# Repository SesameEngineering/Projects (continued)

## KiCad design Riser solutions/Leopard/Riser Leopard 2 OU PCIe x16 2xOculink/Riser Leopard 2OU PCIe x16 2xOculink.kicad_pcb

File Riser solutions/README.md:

# Riser Solutions

Different riser solutions for OCP Leopard and OCP Tioga pass server are available. In those folders you can find different riser designs. For each you will have :
* Design files : all of the file required to do the design. Design has been made usiong Kicad
* Production files : files that you need for production, send all of them to your PCB manufacturer for production (it includes PCB, components and assembly)
* Test report : result of test that has been done to validate the designs

## Riser solutions for Leopard

### Riser 2 OU, 6x Oculink connector

On this riser we have 6 Oculink connector. Each connector is connected to 4 PCie lanes so we use the 24 PCie lanes available from Leopard server. This riser is used for storage solution since we can connect up to 6 U.2 form factor drives. A special cable, Oculink to U.2 has to be used to connect to each drives.

### Riser 2 OU, 1x connector PCIe x16 + 2x Oculink connector

On this riser we have 2 Oculink connector and one x16 PCIe connector. Each Oculink uses 4 PCIe lanes so in total we use the 24 PCIe lanes available from Leopard server. Oculink connectors can be connected to U.2 devices via a Oculink to U.2 cable. Any half length PCIe devices can be connected to the x16 PCIe connector (Ava Board, network card, HBA, small form factor GPUs, etc..).

### Riser 2 OU, 1x connector PCIe x8 + 4x Oculink connector

On this riser we have 4 Oculink connector and one x8 PCIe connector. Each Oculink uses 4 PCIe lanes so in total we use the 24 PCIe lanes available from Leopard server. Oculink connectors can be connected to U.2 devices via a Oculink to U.2 cable. Only x8 PCIe devices can be connected to the x8 PCIe connector.

### Riser 1 OU, 1x connector PCIe x16

This riser is for 1 OU form factor Leopard. There is only one x16 PCIe connector on it so we only use 16 PCIe lanes over the 24 PCIe lanes from Leopard server. Any half length PCIe devices can be connected to the x16 PCIe connector (Ava Board, network card, HBA, small form factor GPUs, etc..).

## Riser solutions for Tioga Pass

### Riser 2 OU, dual connector PCIe x16

This riser has been designed to provide riser to Tioga Pass servers. It has 2 x16 PCIe connectors so it uses the 32 PCIe lanes from Tioga Pass server. Any half length PCIe devices can be connected to the x16 PCIe connector (Ava Board, network card, HBA, small form factor GPUs, etc..). One full length GPU can be connector to the upper PCIe slot

### Riser 1 OU, 1x connector PCIe x16

This riser is for 1 OU form factor Tioga Pass. There is only one x16 PCIe connector on it so we only use 16 PCIe lanes over the 32 PCIe lanes from Tioga Pass server. Any half length PCIe devices can be connected to the x16 PCIe connector (Ava Board, network card, HBA, small form factor GPUs, etc..).

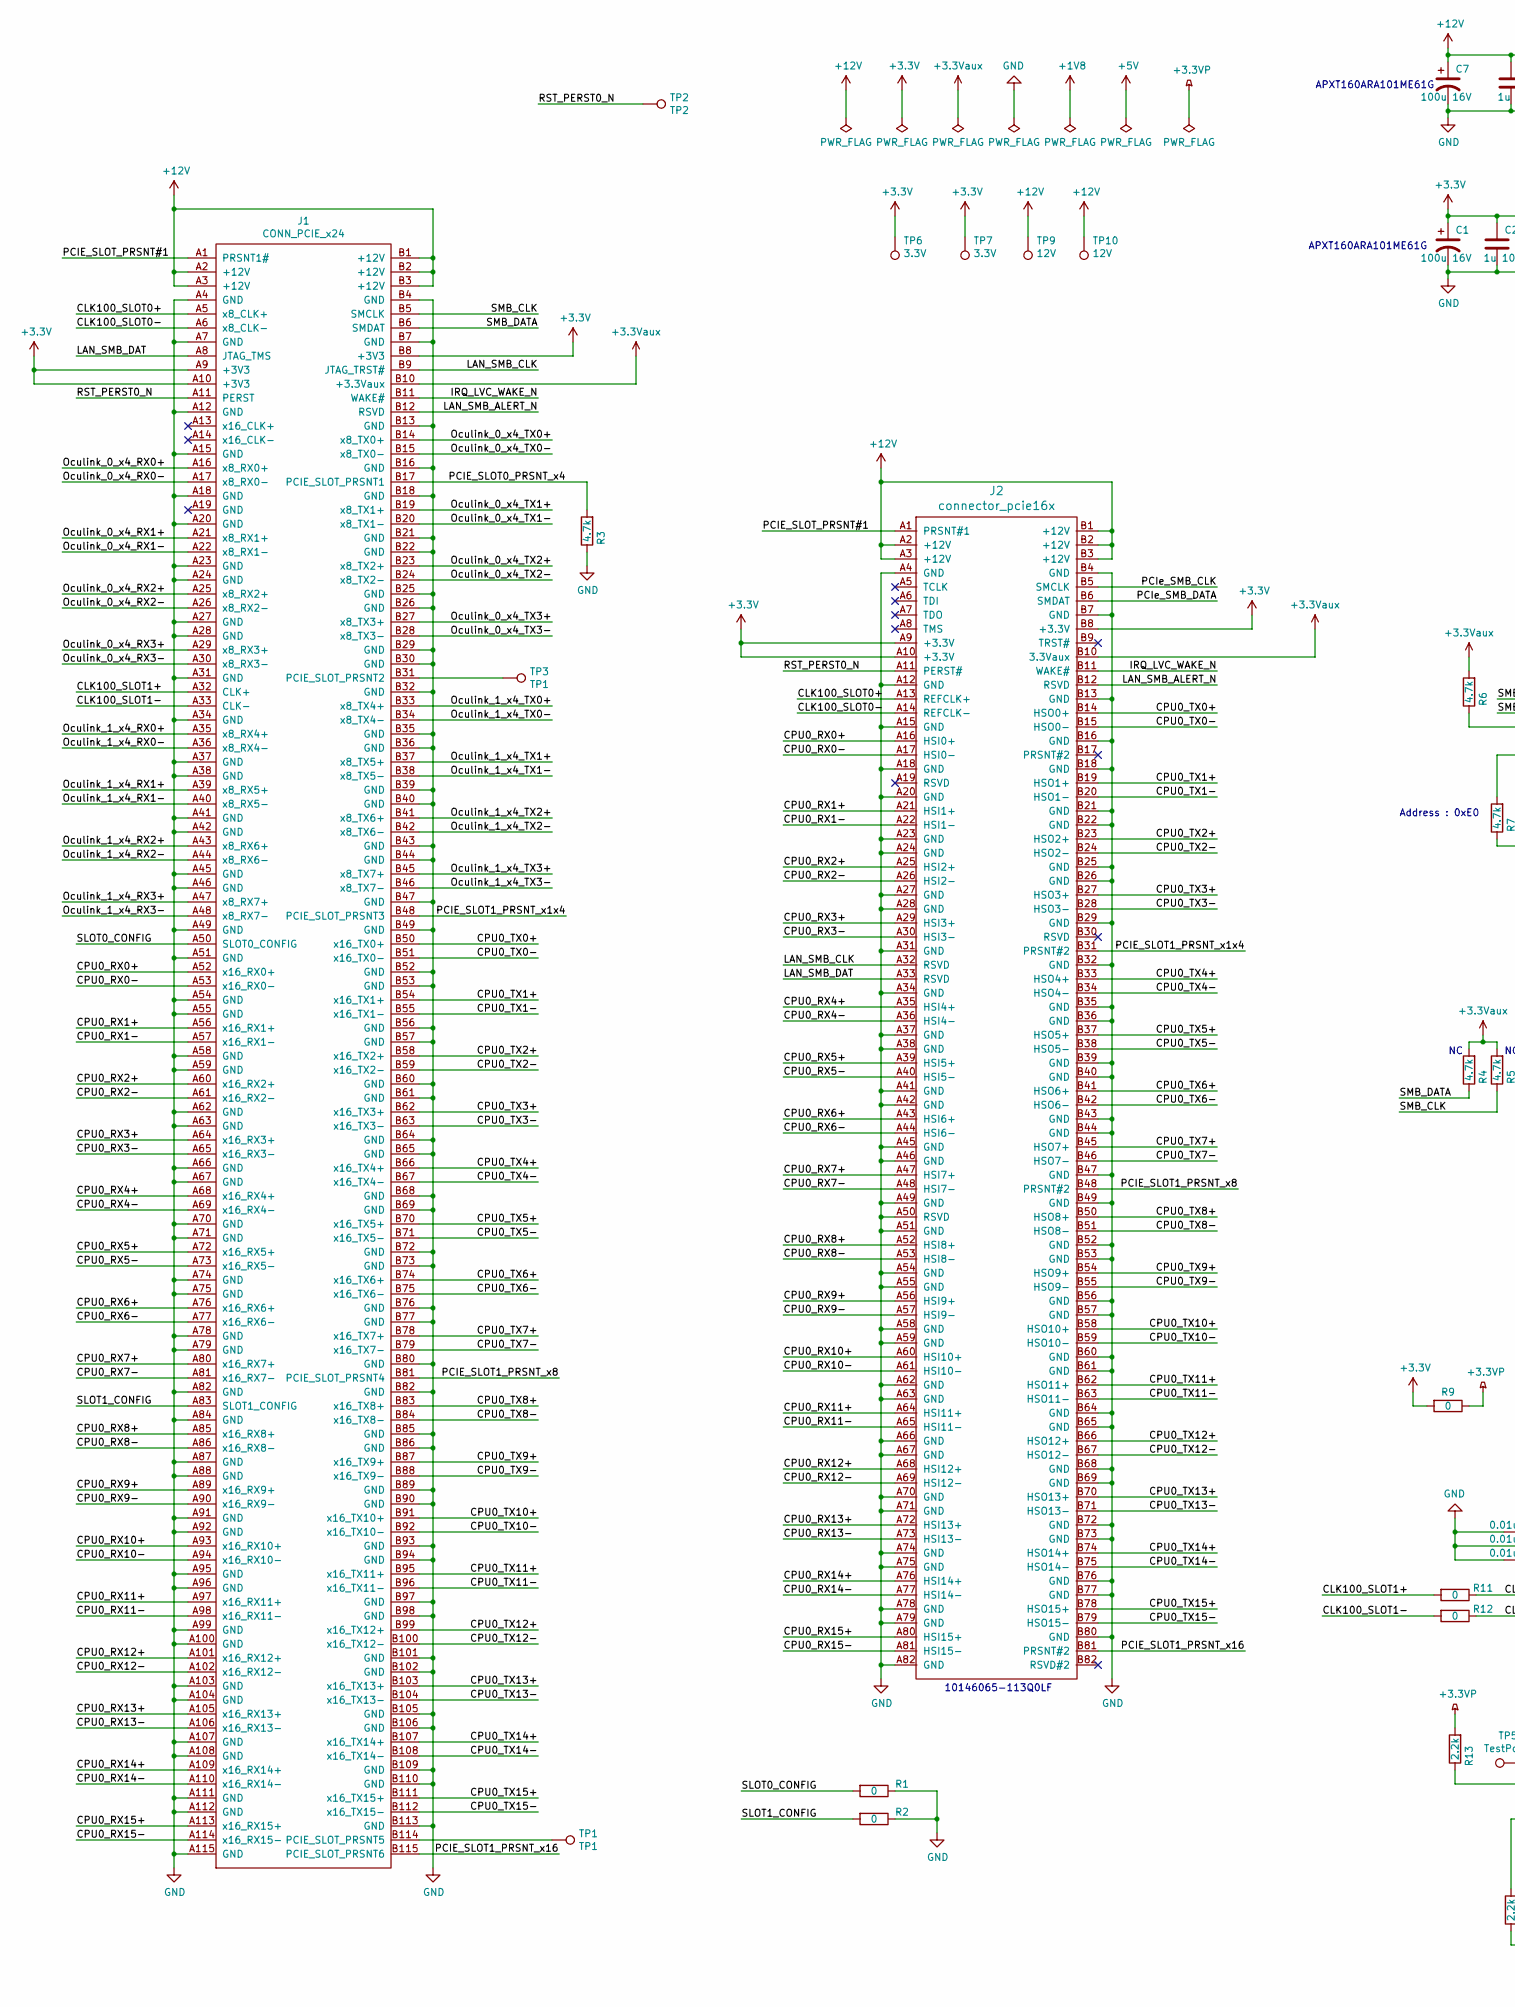
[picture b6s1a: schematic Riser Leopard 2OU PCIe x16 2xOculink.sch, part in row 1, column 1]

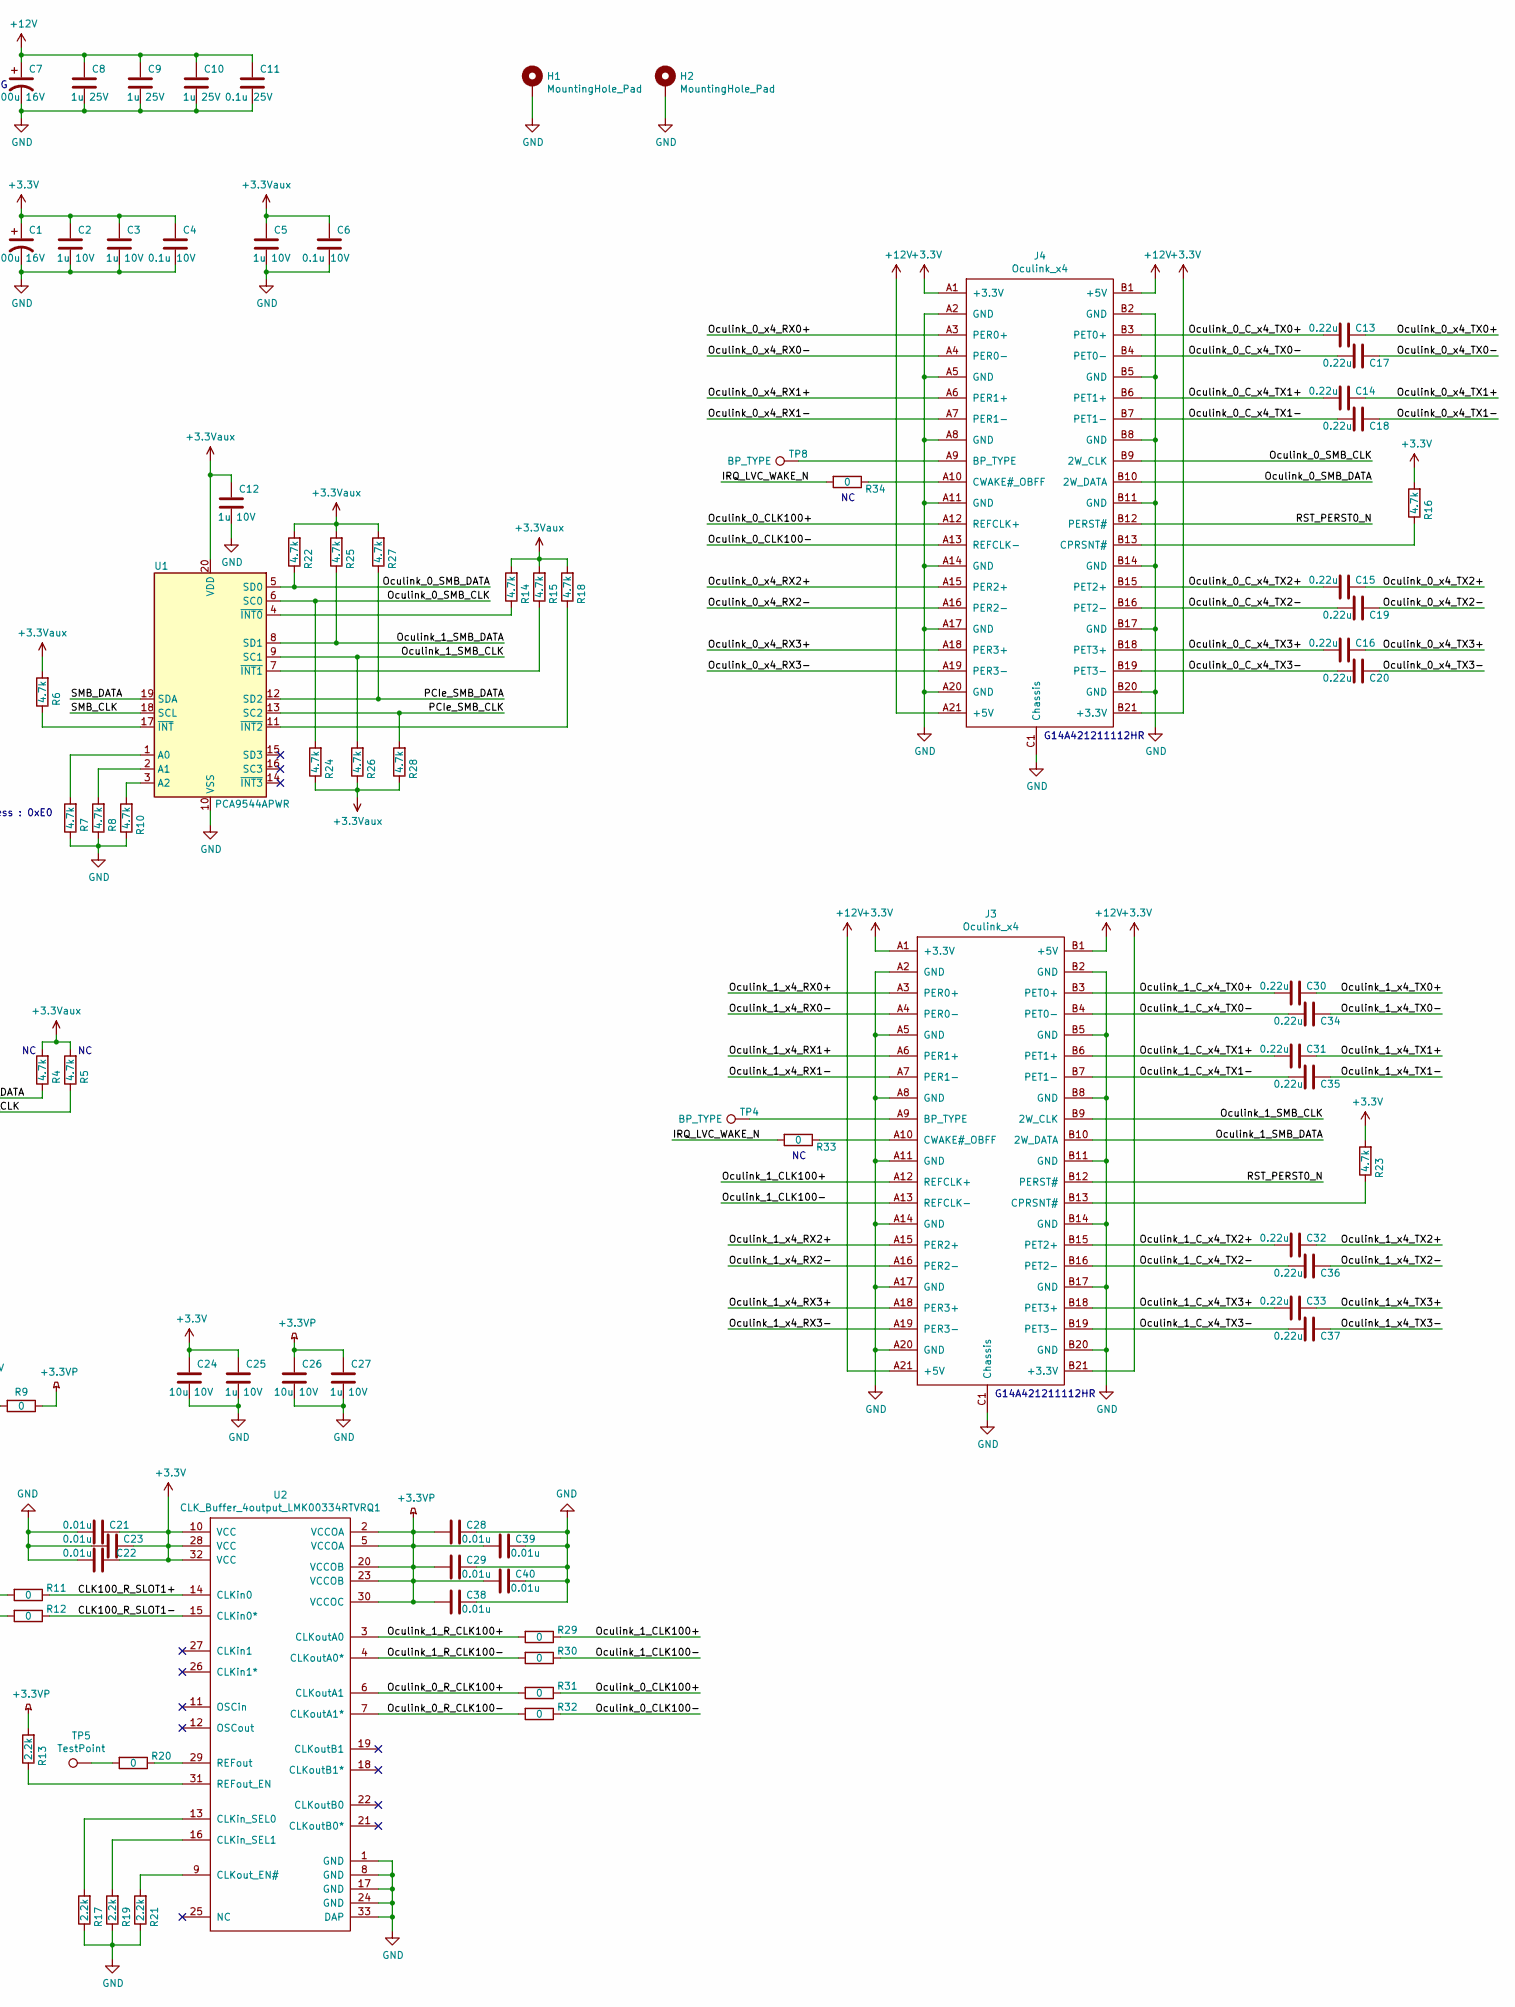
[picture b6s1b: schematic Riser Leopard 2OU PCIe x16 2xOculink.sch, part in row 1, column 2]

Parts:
C1, C7: 100u 16V; CapaElec_100u_16V_5.3x5.3mm
C2, C3, C5, C12, C25, C27: 1u 10V; C_0402
C4, C6: 0.1u 10V; C_0402
C8, C9, C10: 1u 25V; C_0603
C11: 0.1u 25V; C_0402
C13, C14, C15, C16, C17, C18, C19, C20, C30, C31, C32, C33, C34, C35, C36, C37: 0.22u; C_0201
C21, C22, C23, C28, C29, C38, C39, C40: 0.01u; C_0201
C24, C26: 10u 10V; C_0402
H1, H2: MountingHole_Pad; MountingHole_3.2mm_M3_Pad_Via
J1: CONN_PCIE_x24; pads_pcie_x24
J2: connector_pcie16x; pcie_16x
J3, J4: Oculink_x4; Oculink_x4_straight_G14A42221612AHR
R1, R2, R9, R11, R12, R20, R29, R30, R31, R32, R33, R34: 0; R_0402
R3, R4, R5, R6, R7, R8, R10, R14, R15, R16, R18, R22, R23, R24, R25, R26, R27, R28: 4.7k; R_0402
R13, R17, R19, R21: 2.2k; R_0402
TP1, TP3: TP1; TestPoint_Pad_D0.5mm
TP2: TP2; TestPoint_Pad_D0.5mm
TP4, TP8: BP_TYPE; TestPoint_Pad_D0.5mm
TP5: TestPoint; TestPoint_Pad_D0.5mm
TP6, TP7: 3.3V; TestPoint_Pad_D0.5mm
TP9, TP10: 12V; TestPoint_Pad_D0.5mm
U1: PCA9544APWR; TSSOP-20_4.4x6.5mm_Pitch0.65mm
U2: CLK_Buffer_4output_LMK00334RTVRQ1; WQFN-32-1EP_5x5mm_Pitch0.5mm

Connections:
+3.3VP: C26.1, C27.1, C28.2, C29.2, C38.2, C39.2, C40.2, R9.1, R13.2, U2.2 (VCCOA), U2.5 (VCCOA), U2.20 (VCCOB), U2.23 (VCCOB), U2.30 (VCCOC)
+3.3Vaux: C5.1, C6.1, C12.1, J1.B10 (+3.3Vaux), J2.B10 (3.3Vaux), R4.2, R5.2, R6.2, R14.2, R15.2, R18.2, R22.2, R24.1, R25.2, R26.1, R27.2, R28.1, U1.20 (VDD)
+3V3: C1.1, C2.1, C3.1, C4.1, C21.1, C22.1, C23.1, C24.1, C25.1, J1.A9 (+3V3), J1.A10 (+3V3), J1.B8 (+3V3), J2.A9 (+3.3V), J2.A10 (+3.3V), J2.B8 (+3.3V), J3.A1 (+3.3V), J3.B21 (+3.3V), J4.A1 (+3.3V), J4.B21 (+3.3V), R9.2, R16.2, R23.2, TP6.1, TP7.1, U2.10 (VCC), U2.28 (VCC), U2.32 (VCC); also elsewhere on the board
+12V: C7.1, C8.1, C9.1, C10.1, C11.1, J1.A2 (+12V), J1.A3 (+12V), J1.B1 (+12V), J1.B2 (+12V), J1.B3 (+12V), J2.A2 (+12V), J2.A3 (+12V), J2.B1 (+12V), J2.B2 (+12V), J2.B3 (+12V), J3.A21 (+5V), J3.B1 (+5V), J4.A21 (+5V), J4.B1 (+5V), TP9.1, TP10.1; also elsewhere on the board
/CLK100_R_SLOT1+: R11.1, U2.14 (CLKin0)
/CLK100_R_SLOT1-: R12.1, U2.15 (CLKin0*)
/CLK100_SLOT0+: J1.A5 (x8_CLK+), J2.A13 (REFCLK+)
/CLK100_SLOT0-: J1.A6 (x8_CLK-), J2.A14 (REFCLK-)
/CLK100_SLOT1+: J1.A32 (CLK+), R11.2
/CLK100_SLOT1-: J1.A33 (CLK-), R12.2
/CPU0_RX0+: J1.A52 (x16_RX0+), J2.A16 (HSI0+)
/CPU0_RX0-: J1.A53 (x16_RX0-), J2.A17 (HSI0-)
/CPU0_RX1+: J1.A56 (x16_RX1+), J2.A21 (HSI1+)
/CPU0_RX1-: J1.A57 (x16_RX1-), J2.A22 (HSI1-)
/CPU0_RX2+: J1.A60 (x16_RX2+), J2.A25 (HSI2+)
/CPU0_RX2-: J1.A61 (x16_RX2-), J2.A26 (HSI2-)
/CPU0_RX3+: J1.A64 (x16_RX3+), J2.A29 (HSI3+)
/CPU0_RX3-: J1.A65 (x16_RX3-), J2.A30 (HSI3-)
/CPU0_RX4+: J1.A68 (x16_RX4+), J2.A35 (HSI4+)
/CPU0_RX4-: J1.A69 (x16_RX4-), J2.A36 (HSI4-)
/CPU0_RX5+: J1.A72 (x16_RX5+), J2.A39 (HSI5+)
/CPU0_RX5-: J1.A73 (x16_RX5-), J2.A40 (HSI5-)
/CPU0_RX6+: J1.A76 (x16_RX6+), J2.A43 (HSI6+)
/CPU0_RX6-: J1.A77 (x16_RX6-), J2.A44 (HSI6-)
/CPU0_RX7+: J1.A80 (x16_RX7+), J2.A47 (HSI7+)
/CPU0_RX7-: J1.A81 (x16_RX7-), J2.A48 (HSI7-)
/CPU0_RX8+: J1.A85 (x16_RX8+), J2.A52 (HSI8+)
/CPU0_RX8-: J1.A86 (x16_RX8-), J2.A53 (HSI8-)
/CPU0_RX9+: J1.A89 (x16_RX9+), J2.A56 (HSI9+)
/CPU0_RX9-: J1.A90 (x16_RX9-), J2.A57 (HSI9-)
/CPU0_RX10+: J1.A93 (x16_RX10+), J2.A60 (HSI10+)
/CPU0_RX10-: J1.A94 (x16_RX10-), J2.A61 (HSI10-)
/CPU0_RX11+: J1.A97 (x16_RX11+), J2.A64 (HSI11+)
/CPU0_RX11-: J1.A98 (x16_RX11-), J2.A65 (HSI11-)
/CPU0_RX12+: J1.A101 (x16_RX12+), J2.A68 (HSI12+)
/CPU0_RX12-: J1.A102 (x16_RX12-), J2.A69 (HSI12-)
/CPU0_RX13+: J1.A105 (x16_RX13+), J2.A72 (HSI13+)
/CPU0_RX13-: J1.A106 (x16_RX13-), J2.A73 (HSI13-)
/CPU0_RX14+: J1.A109 (x16_RX14+), J2.A76 (HSI14+)
/CPU0_RX14-: J1.A110 (x16_RX14-), J2.A77 (HSI14-)
/CPU0_RX15+: J1.A113 (x16_RX15+), J2.A80 (HSI15+)
/CPU0_RX15-: J1.A114 (x16_RX15-), J2.A81 (HSI15-)
/CPU0_TX0+: J1.B50 (x16_TX0+), J2.B14 (HSO0+)
/CPU0_TX0-: J1.B51 (x16_TX0-), J2.B15 (HSO0-)
/CPU0_TX1+: J1.B54 (x16_TX1+), J2.B19 (HSO1+)
/CPU0_TX1-: J1.B55 (x16_TX1-), J2.B20 (HSO1-)
/CPU0_TX2+: J1.B58 (x16_TX2+), J2.B23 (HSO2+)
/CPU0_TX2-: J1.B59 (x16_TX2-), J2.B24 (HSO2-)
/CPU0_TX3+: J1.B62 (x16_TX3+), J2.B27 (HSO3+)
/CPU0_TX3-: J1.B63 (x16_TX3-), J2.B28 (HSO3-)
/CPU0_TX4+: J1.B66 (x16_TX4+), J2.B33 (HSO4+)
/CPU0_TX4-: J1.B67 (x16_TX4-), J2.B34 (HSO4-)
/CPU0_TX5+: J1.B70 (x16_TX5+), J2.B37 (HSO5+)
/CPU0_TX5-: J1.B71 (x16_TX5-), J2.B38 (HSO5-)
/CPU0_TX6+: J1.B74 (x16_TX6+), J2.B41 (HSO6+)
/CPU0_TX6-: J1.B75 (x16_TX6-), J2.B42 (HSO6-)
/CPU0_TX7+: J1.B78 (x16_TX7+), J2.B45 (HSO7+)
/CPU0_TX7-: J1.B79 (x16_TX7-), J2.B46 (HSO7-)
/CPU0_TX8+: J1.B83 (x16_TX8+), J2.B50 (HSO8+)
/CPU0_TX8-: J1.B84 (x16_TX8-), J2.B51 (HSO8-)
/CPU0_TX9+: J1.B87 (x16_TX9+), J2.B54 (HSO9+)
/CPU0_TX9-: J1.B88 (x16_TX9-), J2.B55 (HSO9-)
/CPU0_TX10+: J1.B91 (x16_TX10+), J2.B58 (HSO10+)
/CPU0_TX10-: J1.B92 (x16_TX10-), J2.B59 (HSO10-)
/CPU0_TX11+: J1.B95 (x16_TX11+), J2.B62 (HSO11+)
/CPU0_TX11-: J1.B96 (x16_TX11-), J2.B63 (HSO11-)
/CPU0_TX12+: J1.B99 (x16_TX12+), J2.B66 (HSO12+)
/CPU0_TX12-: J1.B100 (x16_TX12-), J2.B67 (HSO12-)
/CPU0_TX13+: J1.B103 (x16_TX13+), J2.B70 (HSO13+)
/CPU0_TX13-: J1.B104 (x16_TX13-), J2.B71 (HSO13-)
/CPU0_TX14+: J1.B107 (x16_TX14+), J2.B74 (HSO14+)
/CPU0_TX14-: J1.B108 (x16_TX14-), J2.B75 (HSO14-)
/CPU0_TX15+: J1.B111 (x16_TX15+), J2.B78 (HSO15+)
/CPU0_TX15-: J1.B112 (x16_TX15-), J2.B79 (HSO15-)
/IRQ_LVC_WAKE_N: J1.B11 (WAKE#), J2.B11 (WAKE#), R33.2, R34.2
/LAN_SMB_ALERT_N: J1.B12 (RSVD), J2.B12 (RSVD)
/LAN_SMB_CLK: J1.B9 (JTAG_TRST#), J2.A32 (RSVD)
/LAN_SMB_DAT: J1.A8 (JTAG_TMS), J2.A33 (RSVD)
/Oculink_0_CLK100+: J4.A12 (REFCLK+), R31.1
/Oculink_0_CLK100-: J4.A13 (REFCLK-), R32.1
/Oculink_0_C_x4_TX0+: C13.2, J4.B3 (PET0+)
/Oculink_0_C_x4_TX0-: C17.2, J4.B4 (PET0-)
/Oculink_0_C_x4_TX1+: C14.2, J4.B6 (PET1+)
/Oculink_0_C_x4_TX1-: C18.2, J4.B7 (PET1-)
/Oculink_0_C_x4_TX2+: C15.2, J4.B15 (PET2+)
/Oculink_0_C_x4_TX2-: C19.2, J4.B16 (PET2-)
/Oculink_0_C_x4_TX3+: C16.2, J4.B18 (PET3+)
/Oculink_0_C_x4_TX3-: C20.2, J4.B19 (PET3-)
/Oculink_0_R_CLK100+: R31.2, U2.6 (CLKoutA1)
/Oculink_0_R_CLK100-: R32.2, U2.7 (CLKoutA1*)
/Oculink_0_SMB_CLK: J4.B9 (2W_CLK), R24.2, U1.6 (SC0)
/Oculink_0_SMB_DATA: J4.B10 (2W_DATA), R22.1, U1.5 (SD0)
/Oculink_0_x4_RX0+: J1.A16 (x8_RX0+), J4.A3 (PER0+)
/Oculink_0_x4_RX0-: J1.A17 (x8_RX0-), J4.A4 (PER0-)
/Oculink_0_x4_RX1+: J1.A21 (x8_RX1+), J4.A6 (PER1+)
/Oculink_0_x4_RX1-: J1.A22 (x8_RX1-), J4.A7 (PER1-)
/Oculink_0_x4_RX2+: J1.A25 (x8_RX2+), J4.A15 (PER2+)
/Oculink_0_x4_RX2-: J1.A26 (x8_RX2-), J4.A16 (PER2-)
/Oculink_0_x4_RX3+: J1.A29 (x8_RX3+), J4.A18 (PER3+)
/Oculink_0_x4_RX3-: J1.A30 (x8_RX3-), J4.A19 (PER3-)
/Oculink_0_x4_TX0+: C13.1, J1.B14 (x8_TX0+)
/Oculink_0_x4_TX0-: C17.1, J1.B15 (x8_TX0-)
/Oculink_0_x4_TX1+: C14.1, J1.B19 (x8_TX1+)
/Oculink_0_x4_TX1-: C18.1, J1.B20 (x8_TX1-)
/Oculink_0_x4_TX2+: C15.1, J1.B23 (x8_TX2+)
/Oculink_0_x4_TX2-: C19.1, J1.B24 (x8_TX2-)
/Oculink_0_x4_TX3+: C16.1, J1.B27 (x8_TX3+)
/Oculink_0_x4_TX3-: C20.1, J1.B28 (x8_TX3-)
/Oculink_1_CLK100+: J3.A12 (REFCLK+), R29.1
/Oculink_1_CLK100-: J3.A13 (REFCLK-), R30.1
/Oculink_1_C_x4_TX0+: C30.2, J3.B3 (PET0+)
/Oculink_1_C_x4_TX0-: C34.2, J3.B4 (PET0-)
/Oculink_1_C_x4_TX1+: C31.2, J3.B6 (PET1+)
/Oculink_1_C_x4_TX1-: C35.2, J3.B7 (PET1-)
/Oculink_1_C_x4_TX2+: C32.2, J3.B15 (PET2+)
/Oculink_1_C_x4_TX2-: C36.2, J3.B16 (PET2-)
/Oculink_1_C_x4_TX3+: C33.2, J3.B18 (PET3+)
/Oculink_1_C_x4_TX3-: C37.2, J3.B19 (PET3-)
/Oculink_1_R_CLK100+: R29.2, U2.3 (CLKoutA0)
/Oculink_1_R_CLK100-: R30.2, U2.4 (CLKoutA0*)
/Oculink_1_SMB_CLK: J3.B9 (2W_CLK), R26.2, U1.9 (SC1)
/Oculink_1_SMB_DATA: J3.B10 (2W_DATA), R25.1, U1.8 (SD1)
/Oculink_1_x4_RX0+: J1.A35 (x8_RX4+), J3.A3 (PER0+)
/Oculink_1_x4_RX0-: J1.A36 (x8_RX4-), J3.A4 (PER0-)
/Oculink_1_x4_RX1+: J1.A39 (x8_RX5+), J3.A6 (PER1+)
/Oculink_1_x4_RX1-: J1.A40 (x8_RX5-), J3.A7 (PER1-)
/Oculink_1_x4_RX2+: J1.A43 (x8_RX6+), J3.A15 (PER2+)
/Oculink_1_x4_RX2-: J1.A44 (x8_RX6-), J3.A16 (PER2-)
/Oculink_1_x4_RX3+: J1.A47 (x8_RX7+), J3.A18 (PER3+)
/Oculink_1_x4_RX3-: J1.A48 (x8_RX7-), J3.A19 (PER3-)
/Oculink_1_x4_TX0+: C30.1, J1.B33 (x8_TX4+)
/Oculink_1_x4_TX0-: C34.1, J1.B34 (x8_TX4-)
/Oculink_1_x4_TX1+: C31.1, J1.B37 (x8_TX5+)
/Oculink_1_x4_TX1-: C35.1, J1.B38 (x8_TX5-)
/Oculink_1_x4_TX2+: C32.1, J1.B41 (x8_TX6+)
/Oculink_1_x4_TX2-: C36.1, J1.B42 (x8_TX6-)
/Oculink_1_x4_TX3+: C33.1, J1.B45 (x8_TX7+)
/Oculink_1_x4_TX3-: C37.1, J1.B46 (x8_TX7-)
/PCIE_SLOT0_PRSNT_x4: J1.B17 (PCIE_SLOT_PRSNT1), R3.2
/PCIE_SLOT1_PRSNT_x1x4: J1.B48 (PCIE_SLOT_PRSNT3), J2.B31 (PRSNT#2)
/PCIE_SLOT1_PRSNT_x8: J1.B81 (PCIE_SLOT_PRSNT4), J2.B48 (PRSNT#2)
/PCIE_SLOT1_PRSNT_x16: J1.B115 (PCIE_SLOT_PRSNT6), J2.B81 (PRSNT#2)
/PCIE_SLOT_PRSNT#1: J1.A1 (PRSNT1#), J2.A1 (PRSNT#1)
/PCIe_SMB_CLK: J2.B5 (SMCLK), R28.2, U1.13 (SC2)
/PCIe_SMB_DATA: J2.B6 (SMDAT), R27.1, U1.12 (SD2)
/RST_PERST0_N: J1.A11 (PERST), J2.A11 (PERST#), J3.B12 (PERST#), J4.B12 (PERST#), TP2.1
/SLOT0_CONFIG: J1.A50 (SLOT0_CONFIG), R1.2
/SLOT1_CONFIG: J1.A83 (SLOT1_CONFIG), R2.2
/SMB_CLK: J1.B5 (SMCLK), R5.1, U1.18 (SCL)
/SMB_DATA: J1.B6 (SMDAT), R4.1, U1.19 (SDA)
GND: C1.2, C2.2, C3.2, C4.2, C5.2, C6.2, C7.2, C8.2, C9.2, C10.2, C11.2, C12.2, C21.2, C22.2, C23.2, C24.2, C25.2, C26.2, C27.2, C28.1, C29.1, C38.1, C39.1, C40.1, H1.1, H2.1, J1.A4 (GND), J1.A7 (GND), J1.A12 (GND), J1.A15 (GND), J1.A18 (GND), J1.A20 (GND), J1.A23 (GND), J1.A24 (GND), J1.A27 (GND), J1.A28 (GND), J1.A31 (GND), J1.A34 (GND), J1.A37 (GND), J1.A38 (GND), J1.A41 (GND), J1.A42 (GND), J1.A45 (GND), J1.A46 (GND), J1.A49 (GND), J1.A51 (GND), J1.A54 (GND), J1.A55 (GND), J1.A58 (GND), J1.A59 (GND), J1.A62 (GND), J1.A63 (GND), J1.A66 (GND), J1.A67 (GND), J1.A70 (GND), J1.A71 (GND), J1.A74 (GND), J1.A75 (GND), J1.A78 (GND), J1.A79 (GND), J1.A82 (GND), J1.A84 (GND), J1.A87 (GND), J1.A88 (GND), J1.A91 (GND), J1.A92 (GND), J1.A95 (GND), J1.A96 (GND), J1.A99 (GND), J1.A100 (GND), J1.A103 (GND), J1.A104 (GND), J1.A107 (GND), J1.A108 (GND), J1.A111 (GND), J1.A112 (GND), J1.A115 (GND), J1.B4 (GND), J1.B7 (GND), J1.B13 (GND), J1.B16 (GND), J1.B18 (GND), J1.B21 (GND), J1.B22 (GND), J1.B25 (GND), J1.B26 (GND), J1.B29 (GND), J1.B30 (GND), J1.B32 (GND), J1.B35 (GND), J1.B36 (GND), J1.B39 (GND), J1.B40 (GND), J1.B43 (GND), J1.B44 (GND), J1.B47 (GND), J1.B49 (GND), J1.B52 (GND), J1.B53 (GND), J1.B56 (GND), J1.B57 (GND), J1.B60 (GND), J1.B61 (GND), J1.B64 (GND), J1.B65 (GND), J1.B68 (GND), J1.B69 (GND), J1.B72 (GND), J1.B73 (GND), J1.B76 (GND), J1.B77 (GND), J1.B80 (GND), J1.B82 (GND), J1.B85 (GND), J1.B86 (GND), J1.B89 (GND), J1.B90 (GND), J1.B93 (GND), J1.B94 (GND), J1.B97 (GND), J1.B98 (GND), J1.B101 (GND), J1.B102 (GND), J1.B105 (GND), J1.B106 (GND), J1.B109 (GND), J1.B110 (GND), J1.B113 (GND), J2.A4 (GND), J2.A12 (GND), J2.A15 (GND), J2.A18 (GND), J2.A20 (GND), J2.A23 (GND), J2.A24 (GND), J2.A27 (GND), J2.A28 (GND), J2.A31 (GND), J2.A34 (GND), J2.A37 (GND), J2.A38 (GND), J2.A41 (GND), J2.A42 (GND), J2.A45 (GND), J2.A46 (GND), J2.A49 (GND), J2.A50 (RSVD), J2.A51 (GND), J2.A54 (GND), J2.A55 (GND), J2.A58 (GND), J2.A59 (GND), J2.A62 (GND), J2.A63 (GND), J2.A66 (GND), J2.A67 (GND), J2.A70 (GND), J2.A71 (GND), J2.A74 (GND), J2.A75 (GND), J2.A78 (GND), J2.A79 (GND), J2.A82 (GND), J2.B4 (GND), J2.B7 (GND), J2.B13 (GND), J2.B16 (GND), J2.B18 (GND), J2.B21 (GND), J2.B22 (GND), J2.B25 (GND), J2.B26 (GND), J2.B29 (GND), J2.B32 (GND), J2.B35 (GND), J2.B36 (GND), J2.B39 (GND), J2.B40 (GND), J2.B43 (GND), J2.B44 (GND), J2.B47 (GND), J2.B49 (GND), J2.B52 (GND), J2.B53 (GND), J2.B56 (GND), J2.B57 (GND), J2.B60 (GND), J2.B61 (GND), J2.B64 (GND), J2.B65 (GND), J2.B68 (GND), J2.B69 (GND), J2.B72 (GND), J2.B73 (GND), J2.B76 (GND), J2.B77 (GND), J2.B80 (GND), J3.A2 (GND), J3.A5 (GND), J3.A8 (GND), J3.A11 (GND), J3.A14 (GND), J3.A17 (GND), J3.A20 (GND), J3.B2 (GND), J3.B5 (GND), J3.B8 (GND), J3.B11 (GND), J3.B14 (GND), J3.B17 (GND), J3.B20 (GND), J3.C1 (Chassis), J4.A2 (GND), J4.A5 (GND), J4.A8 (GND), J4.A11 (GND), J4.A14 (GND), J4.A17 (GND), J4.A20 (GND), J4.B2 (GND), J4.B5 (GND), J4.B8 (GND), J4.B11 (GND), J4.B14 (GND), J4.B17 (GND), J4.B20 (GND), J4.C1 (Chassis), R1.1, R2.1, R3.1, R7.1, R8.1, R10.1, R17.1, R19.1, R21.1, U1.10 (VSS), U2.1 (GND), U2.8 (GND), U2.17 (GND), U2.24 (GND), U2.33 (DAP)
unnamed: J1.B31 (PCIE_SLOT_PRSNT2), TP3.1
unnamed: J1.B114 (PCIE_SLOT_PRSNT5), TP1.1
unnamed: J3.A9 (BP_TYPE), TP4.1
unnamed: J3.A10 (CWAKE#_OBFF), R33.1
unnamed: J3.B13 (CPRSNT#), R23.1
unnamed: J4.A9 (BP_TYPE), TP8.1
unnamed: J4.A10 (CWAKE#_OBFF), R34.1
unnamed: J4.B13 (CPRSNT#), R16.1
unnamed: R6.1, U1.17 (~INT)
unnamed: R7.2, U1.1 (A0)
unnamed: R8.2, U1.2 (A1)
unnamed: R10.2, U1.3 (A2)
unnamed: R13.1, U2.31 (REFout_EN)
unnamed: R14.1, U1.4 (~INT0)
unnamed: R15.1, U1.7 (~INT1)
unnamed: R17.2, U2.13 (CLKin_SEL0)
unnamed: R18.1, U1.11 (~INT2)
unnamed: R19.2, U2.16 (CLKin_SEL1)
unnamed: R20.1, U2.29 (REFout)
unnamed: R20.2, TP5.1
unnamed: R21.2, U2.9 (CLKout_EN#)

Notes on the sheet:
APXT160ARA101ME61G
10146065-113Q0LF
G14A421211112HR
Address : 0xE0

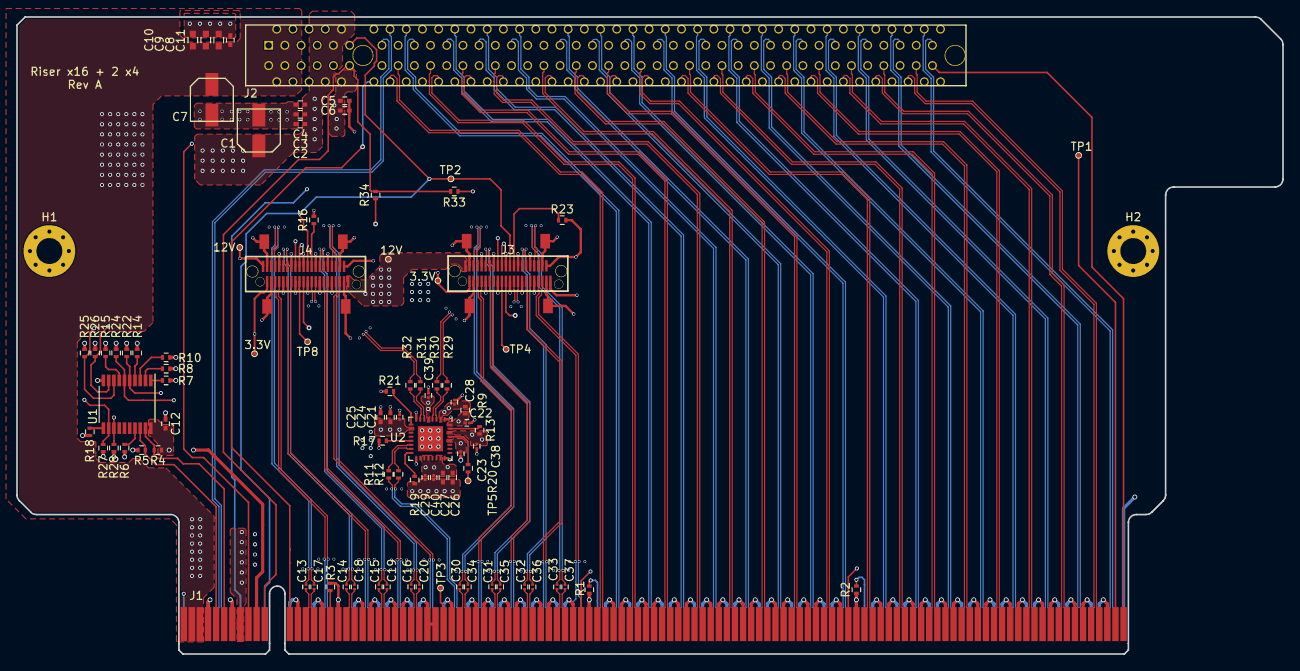
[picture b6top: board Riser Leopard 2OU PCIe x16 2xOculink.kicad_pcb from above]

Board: 6 copper layers, 156.4 x 78.7 mm, 92 parts (0 on the bottom side), 172 nets.

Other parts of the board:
3.3V, 3.3V#2: 3.3V; TestPoint_Pad_D0.5mm
12V, 12V#2: 12V; TestPoint_Pad_D0.5mm

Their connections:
+3V3: 3.3V.1, 3.3V#2.1; also elsewhere on the board
+12V: 12V.1, 12V#2.1; also elsewhere on the board

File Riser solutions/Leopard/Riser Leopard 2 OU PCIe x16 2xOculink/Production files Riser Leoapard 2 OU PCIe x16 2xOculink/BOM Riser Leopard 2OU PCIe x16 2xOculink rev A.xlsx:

Id | Reference | Footprint | Quantity | Designation | Manufacturer | Manufacturer part number
1 | C1,C7 | CapaElec_100u_16V_5.3x5.3mm | 2 | 100u 16V | Panasonic | EEE-FN1C101UR
2 | C2,C3,C5,C12,C25,C27 | C_0402 | 6 | 1u 10V | Taiyo Yuden | LMK105BJ105MVHF
3 | C4,C6 | C_0402 | 2 | 0.1u 10V | Taiyo Yuden | LMF105B7104MVHF
4 | C8,C9,C10 | C_0603 | 3 | 1u 25V | Taiyo Yuden | TMK107B7105KA-T
5 | C11 | C_0402 | 1 | 0.1u 25V | Taiyo Yuden | TMK105B7104MV-FR
6 | C13,C14,C15,C16,C17,C18,C19,C20,C30,C31,C32,C33,C34,C35,C36,C37 | C_0201 | 16 | 0.22u | Murata Electronics | GRM033R61C224KE14J
7 | C21,C22,C23,C28,C29,C38,C39,C40 | C_0201 | 8 | 0.01u | Murata Electronics | GRM033R71A103KA01D
8 | C24,C26 | C_0402 | 2 | 10u 10V | Samsung Electro-Mechanics | CL05A106MP5NUNC
9 | J2 | pcie_16x | 1 | connector_pcie16x | Molex | 87715-9306
10 | J3,J4 | Oculink_x4_straight_G14A42221612AHR | 2 | Oculink_x4 | Amphenol Commercial Products | G14A42221612AHR
11 | R1,R2,R9,R11,R12,R20,R29,R30,R31,R32,R33,R34 | R_0402 | 12 | 0 | Bourns | CR0402-J/-000GLF
12 | R3,R4,R5,R6,R7,R8,R10,R14,R15,R16,R18,R22,R23,R24,R25,R26,R27,R28 | R_0402 | 18 | 4.7k | ROHM Semiconductor | SFR01MZPF4701
13 | R13,R17,R19,R21 | R_0402 | 4 | 2.2k | ROHM Semiconductor | SFR01MZPF2201
14 | U1 | TSSOP-20_4.4x6.5mm_Pitch0.65mm | 1 | PCA9544APWR | Texas Instruments | PCA9544APWR
15 | U2 | WQFN-32-1EP_5x5mm_Pitch0.5mm | 1 | CLK_Buffer_4output_LMK00334RTVRQ1 | Texas Instruments | LMK00334RTVRQ1
